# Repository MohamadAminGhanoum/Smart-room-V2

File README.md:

# Smart-room-V2
I have since around 1 year done a smart room, where i made a custom pcb, and salvaged some parts from an old laptop motherboard to be able to control the LED strip that i have and also open and close my curtain, but that was all my thing could do, this time, im planning on making my pcb using jlcpcb instead of for better quality, and im planning on adding a lot more features, such as a screen, CAD and sensor and this stuff.

Note: The Firmware is currently only a test rn, i will upload a working code, once i make this work.

If you are interested, you can check out my V1 of this, with diy pcb: https://github.com/MohamadAminGhanoum/Smart-home

## Schematics:

## PCB + 3d view:

## Fully assembled CAD:

## BOM

|Id |Designator                  |Footprint                                          |Quantity                             |Price in USD|Designation                |Supplier and ref|Link                                                                                                                                                                                                                                                                                                                                               |
|---|----------------------------|---------------------------------------------------|-------------------------------------|------------|---------------------------|----------------|---------------------------------------------------------------------------------------------------------------------------------------------------------------------------------------------------------------------------------------------------------------------------------------------------------------------------------------------------|
|1  |R14,R13,R10,R15,R12,R11     |R_0603_1608Metric                                  |6                                    |0           |4.7k                       |Self-sourced    |https://www.lcsc.com/product-detail/C99782.html?spm=wm.ddx.16.xqy___wm.ddl.ddb.3.ddh&lcsc_vid=T1FYAQdRRlJYVlZTQldcX11eQ1FfUlFUElBWUQFVQgIxVlNeQ1heVlxSRFBfVzsOAxUeFF5JWBEPFBcWGBMaSQgFBAJABAsLWA%3D%3D                                                                                                                                             |
|2  |2pins socket                |PinSocket_1x02_P2.54mm_Vertical                    |15                                   |1.38        |female socket              |LCSC            |https://www.lcsc.com/product-detail/C7499322.html?s_z=n_q_Female%2520Header%25202%2520Position%25202.54mm%2520Pitch%2520Single%2520Row&spm=wm.fly.bg.0.stp&lcsc_vid=T1FYAQdRRlJYVlZTQldcX11eQ1FfUlFUElBWUQFVQgIxVlNeQlBbV1dVTlNWXjsOAxUeFF5JWBYZEEoKFBINSQcJGk4NBhADEA4cHktRTlJADxALGw%3D%3D                                                       |
|3  |R4                          |R_0603_1608Metric                                  |1                                    |0           |1k                         |self-sourced    |https://www.lcsc.com/product-detail/C22548.html?spm=wm.ddx.12.xqy___wm.ddl.ddb.3.ddh&lcsc_vid=T1FYAQdRRlJYVlZTQldcX11eQ1FfUlFUElBWUQFVQgIxVlNeQ1heVlxSRFBfVzsOAxUeFF5JWBEPFBcWGBMaSQgFBAJABAsLWA%3D%3D                                                                                                                                             |
|4  |R                           |R_0603_1608Metric                                  |100                                  |0.51        |0.1R                       |LCSC            |https://www.lcsc.com/product-detail/C3013345.html?s_z=n_q_t_0.1R%25200603&spm=wm.fly.bg.0.stp___wm.ssy.tc.2.tz&lcsc_vid=T1FYAQdRRlJYVlZTQldcX11eQ1FfUlFUElBWUQFVQgIxVlNeQlBbV1VXR1BcXzsOAxUeFF5JWBYZEEoKFBINSQcJGk4NBhADEA4cHktXR1NXSQwSGg0%3D                                                                                                     |
|5  |R9,R16,R5,R7,R3,R2,R17,R18  |R_0603_1608Metric                                  |8                                    |0           |10k                        |self-sourced    |https://www.lcsc.com/product-detail/C2930027.html?spm=wm.ddx.13.xqy___wm.ddl.ddb.0.ddh&lcsc_vid=T1FYAQdRRlJYVlZTQldcX11eQ1FfUlFUElBWUQFVQgIxVlNeQ1heVlxSRFBfVzsOAxUeFF5JWBEPFBcWGBMaSQgFBAJABAsLWA%3D%3D                                                                                                                                           |
|6  |C15,C8,C12,C1               |C_0603_1608Metric                                  |50                                   |1.15        |1uF                        |LCSC            |https://www.lcsc.com/product-detail/C29936.html?s_z=n_q_t_1uf%25200603&spm=wm.fly.bg.0.stp___wm.ssy.tc.0.tz&lcsc_vid=T1FYAQdRRlJYVlZTQldcX11eQ1FfUlFUElBWUQFVQgIxVlNeQlBaX1ZVT1hZUTsOAxUeFF5JWBYZEEoKFBINSQcJGk4NBhYS                                                                                                                              |
|7  |Q1                          |SOT-23                                             |20                                   |0.74        |AO3400A                    |LCSC            |https://www.lcsc.com/product-detail/C347475.html?s_z=n_q_AO3400A&spm=wm.fly.bg.1.stp&lcsc_vid=T1FYAQdRRlJYVlZTQldcX11eQ1FfUlFUElBWUQFVQgIxVlNeQlBaX1dSQ1FcUDsOAxUeFF5JWBYZEEoKFBINSQcJGk4NBhADEA4cHktXRlVcSQwSGg0%3D                                                                                                                               |
|8  |L1                          |L_10.4x10.4_H4.8                                   |5                                    |0.4         |22uH                       |LCSC            |https://www.lcsc.com/product-detail/C5349702.html?s_z=n_q_p_22uH%2520inductor%252010.4x10.4&spm=wm.ssy.bg.0.stp&lcsc_vid=T1FYAQdRRlJYVlZTQldcX11eQ1FfUlFUElBWUQFVQgIxVlNeQlBaX1BQQFBZUDsOAxUeFF5JWBYZEEoKFBINSQcJGk4NBhADEA4cHktXRllfSQwSGg0%3D                                                                                                    |
|9  |E-ink                       |PinSocket_1x08_P2.54mm_Vertical                    |5                                    |1.69        |E-ink waveshare            |lcSC            |https://www.lcsc.com/product-detail/C2848409.html?s_z=n_q_t_Female%2520Header%25208%2520Position%25202.54mm%2520Pitch%2520Single%2520Row&spm=wm.fly.bg.0.stp___wm.ssy.tc.0.tz&lcsc_vid=T1FYAQdRRlJYVlZTQldcX11eQ1FfUlFUElBWUQFVQgIxVlNeQlBbV1ZeT1NZUjsOAxUeFF5JWBYZEEoKFBINSQcJGk4dAgUUFAk%3D                                                      |
|10 |U1                          |ESP32-S3-WROOM-1                                   |2                                    |9.37        |ESP32-S3-WROOM-1           |LCSC            |https://www.lcsc.com/product-detail/C2913197.html?spm=wm.ddx.22.xqy___wm.ddl.ddb.3.ddh&lcsc_vid=T1FYAQdRRlJYVlZTQldcX11eQ1FfUlFUElBWUQFVQgIxVlNeQ1heVlxSRFBfVzsOAxUeFF5JWBEPFBcWGBMaSQgFBAJABAsLWA%3D%3D                                                                                                                                           |
|11 |U6                          |Sensirion_DFN-4_1.5x1.5mm_P0.8mm_SHT4x_NoCentralPad|2                                    |1.91        |SHT4x                      |LCSC            |https://www.lcsc.com/product-detail/C54946589.html?s_z=n_q_sht40&spm=wm.fly.bg.1.stp&lcsc_vid=T1FYAQdRRlJYVlZTQldcX11eQ1FfUlFUElBWUQFVQgIxVlNeQlBaX1xRRlhcUDsOAxUeFF5JWBYZEEoKFBINSQcJGk4dAgUUFAk%3D                                                                                                                                               |
|12 |SW1                         |SW_SPST_TS-1088-xR020                              |1                                    |0           |Boot                       |Self-sourced    |N/A                                                                                                                                                                                                                                                                                                                                                |
|13 |C2,C14,C9,C10,C3,C13        |C_0603_1608Metric                                  |20                                   |1.9         |10uF                       |LCSC            |https://www.lcsc.com/product-detail/C96446.html?s_z=n_q_t_10uF%25200603&spm=wm.fly.bg.0.stp___wm.ssy.tc.0.tz&lcsc_vid=T1FYAQdRRlJYVlZTQldcX11eQ1FfUlFUElBWUQFVQgIxVlNeQlBaXlRTR1NfVDsOAxUeFF5JWBYZEEoKFBINSQcJGk4eFQsCAgIaSgADAwAHC0slQlVXU1JTT1hADxALGw%3D%3D                                                                                     |
|14 |R1                          |R_0603_1608Metric                                  |100                                  |0.39        |6.8k                       |LCSC            |https://www.lcsc.com/product-detail/C844805.html?s_z=n_q_t_6.8k%25200603&spm=wm.fly.bg.2.stp&lcsc_vid=T1FYAQdRRlJYVlZTQldcX11eQ1FfUlFUElBWUQFVQgIxVlNeQlBaXlVUQ1JYVDsOAxUeFF5JWBYZEEoKFBINSQcJGk4dAgUUFAk%3D                                                                                                                                       |
|15 |C16,C11                     |C_0603_1608Metric                                  |2                                    |0           |100nF                      |self-sourced    |https://www.lcsc.com/product-detail/C1591.html?spm=wm.ddx.12.xqy___wm.ddl.ddb.0.ddh&lcsc_vid=T1FYAQdRRlJYVlZTQldcX11eQ1FfUlFUElBWUQFVQgIxVlNeQ1heVlxSRFBfVzsOAxUeFF5JWBEPFBcWGBMaSQgFBAJABAsLWA%3D%3D                                                                                                                                              |
|16 |RV1                         |JST_XH_B3B-XH-A_1x03_P2.50mm_Vertical              |5                                    |2.7         |R_Potentiometer            |aliexpress      |https://www.aliexpress.com/item/1005003161558340.html?spm=a2g0o.detail.0.0.319b257eU1NCPv&mp=1&pdp_npi=6%40dis%21USD%21USD%202.70%21USD%202.70%21%21USD%202.70%21%21%21%4021613ab217851479801197318e100d%2112000024425220398%21ct%21DK%213871794027%21%211%210%21&pdp_ext_f=%7B%22cart2PdpParams%22%3A%7B%22pdpBusinessMode%22%3A%22retail%22%7D%7D|
|17 |BT1                         |BatteryHolder_Keystone_1058_1x2032                 |2                                    |2.74        |Battery_Cell               |LCSC            |https://www.lcsc.com/product-detail/C5470546.html?s_z=n_q_p_BatteryHolder_Keystone_1058_1x2032&spm=wm.ssy.bg.1.stp&lcsc_vid=T1FYAQdRRlJYVlZTQldcX11eQ1FfUlFUElBWUQFVQgIxVlNeQlBaXlZWTlNaVDsOAxUeFF5JWBYZEEoKFBINSQcJGk4NBhADEA4cHktXRlVcSQwSGg0%3D                                                                                                 |
|18 |D2,D3                       |D_SMA                                              |20                                   |0.54        |SS34                       |LCSC            |https://www.lcsc.com/product-detail/C2837271.html?s_z=n_q_t_SS34&spm=wm.fly.bg.3.stp___wm.ssy.tc.0.tz&lcsc_vid=T1FYAQdRRlJYVlZTQldcX11eQ1FfUlFUElBWUQFVQgIxVlNeQlBbV1NfTlJcVjsOAxUeFF5JWBYZEEoKFBINSQcJGk4NBhADEA4cHktXQ1JeSQwSGg0%3D                                                                                                              |
|19 |R8                          |R_0603_1608Metric                                  |100                                  |0.21        |100R                       |LCSC            |https://www.lcsc.com/product-detail/C2906981.html?s_z=n_q_t_100%25CE%25A9%25200603&spm=wm.fly.bg.0.stp___wm.ssy.tc.0.tz&lcsc_vid=T1FYAQdRRlJYVlZTQldcX11eQ1FfUlFUElBWUQFVQgIxVlNeQlBaXldeRlFeUDsOAxUeFF5JWBYZEEoKFBINSQcJGk4dAgUUFAk%3D                                                                                                            |
|20 |R19,R20                     |R_0603_1608Metric                                  |2                                    |0           |33R                        |self-sourced    |https://www.lcsc.com/product-detail/C2909394.html?spm=wm.ddx.11.xqy___wm.ddl.ddb.0.ddh&lcsc_vid=T1FYAQdRRlJYVlZTQldcX11eQ1FfUlFUElBWUQFVQgIxVlNeQ1heVlxSRFBfVzsOAxUeFF5JWBEPFBcWGBMaSQgFBAJABAsLWA%3D%3D                                                                                                                                           |
|21 |C4                          |C_0603_1608Metric                                  |50                                   |0.8         |0.01uF                     |LCSC            |https://www.lcsc.com/product-detail/C100042.html?s_z=n_q_t_10nf%25200603&spm=wm.fly.bg.0.stp___wm.ssy.tc.0.tz&lcsc_vid=T1FYAQdRRlJYVlZTQldcX11eQ1FfUlFUElBWUQFVQgIxVlNeQlBaXlBfRFFeUzsOAxUeFF5JWBYZEEoKFBINSQcJGk4NBhADEA4cHktXRlhXSQwSGg0%3D                                                                                                      |
|22 |C17,C7                      |CP_Elec_6.3x7.7                                    |5                                    |0.55        |220uF                      |LCSC            |https://www.lcsc.com/product-detail/C2827940.html?s_z=n_q_220uF%25206.3x7.7&spm=wm.fly.bg.0.xh&lcsc_vid=T1FYAQdRRlJYVlZTQldcX11eQ1FfUlFUElBWUQFVQgIxVlNeQlBaXlFSR1VbXzsOAxUeFF5JWBYZEEoKFBINSQcJGk4NBhADEA4cHktXRlVcSQwSGg0%3D                                                                                                                     |
|23 |R6                          |R_0603_1608Metric                                  |100                                  |0.3         |3.24k                      |LCSC            |https://www.lcsc.com/product-detail/C22994.html?s_z=n_q_t_3.24k%25200603&spm=wm.fly.bg.0.stp___wm.ssy.tc.0.tz&lcsc_vid=T1FYAQdRRlJYVlZTQldcX11eQ1FfUlFUElBWUQFVQgIxVlNeQlBaXlJUQVBeUjsOAxUeFF5JWBYZEEoKFBINSQcJGk4NBhADEA4cHktXRlVeSQwSGg0%3D                                                                                                      |
|24 |C5,C6                       |C_0603_1608Metric                                  |2                                    |0           |4.7uF                      |self-sourced    |https://www.lcsc.com/product-detail/C6119856.html?spm=wm.ddx.9.xqy___wm.ddl.ddb.3.ddh&lcsc_vid=T1FYAQdRRlJYVlZTQldcX11eQ1FfUlFUElBWUQFVQgIxVlNeQ1heVlxSRFBfVzsOAxUeFF5JWBEPFBcWGBMaSQgFBAJABAsLWA%3D%3D                                                                                                                                            |
|25 |U4                          |SSOP-10-1EP_3.9x4.9mm_P1mm_EP2.1x3.3mm             |4                                    |1.96        |CH224K                     |lcSC            |https://www.lcsc.com/product-detail/C970725.html?s_z=n_q_CH224K&spm=wm.fly.bg.0.stp&lcsc_vid=T1FYAQdRRlJYVlZTQldcX11eQ1FfUlFUElBWUQFVQgIxVlNeQlBaXlNXR1FYXjsOAxUeFF5JWBYZEEoKFBINSQcJGk4NBhADEA4cHktXRlhXSQwSGg0%3D                                                                                                                                |
|26 |U7                          |SOIC-8_3.9x4.9mm_P1.27mm                           |1                                    |0           |Motor controller, AM4969   |self-sourced    |From robot vacuum                                                                                                                                                                                                                                                                                                                                  |
|27 |D1                          |D_SMC                                              |5                                    |1.13        |B340                       |lcSC            |https://www.lcsc.com/product-detail/C110486.html?s_z=n_q_t_b340&spm=wm.fly.bg.8.stp___wm.ssy.tc.0.tz&lcsc_vid=T1FYAQdRRlJYVlZTQldcX11eQ1FfUlFUElBWUQFVQgIxVlNeQlBbV1JWQ1FcVjsOAxUeFF5JWBYZEEoKFBINSQcJGk4eFQsCAgIaSgADAwAHC0slQFVXXldURU8GEwkK                                                                                                     |
|28 |C18                         |C_0603_1608Metric                                  |1                                    |0           |0.1uF                      |self-sourced    |https://www.lcsc.com/product-detail/C1591.html?spm=wm.ddx.12.xqy___wm.ddl.ddb.0.ddh&lcsc_vid=T1FYAQdRRlJYVlZTQldcX11eQ1FfUlFUElBWUQFVQgIxVlNeQ1heVlxSRFBfVzsOAxUeFF5JWBEPFBcWGBMaSQgFBAJABAsLWA%3D%3D                                                                                                                                              |
|29 |U5                          |SOIC-16W_7.5x10.3mm_P1.27mm                        |1                                    |8.77        |DS3231M                    |lcSC            |https://www.lcsc.com/product-detail/C37663.html?spm=wm.gwc.xh.21.tp___wm.fly.ssl.gwc&lcsc_vid=T1FYAQdRRlJYVlZTQldcX11eQ1FfUlFUElBWUQFVQgIxVlNeQlBbV1dVTlNWXjsOAxUeFF5JWBYZEEoKFBINSQcJGk4NBhADEA4cHktRTlJADxALGw%3D%3D                                                                                                                             |
|30 |U3                          |SOT-23-5                                           |5                                    |0.84        |AP2112K-3.3                |lcSC            |https://www.lcsc.com/product-detail/C51118.html?s_z=n_q_AP2112K-3.3&spm=wm.fly.bg.0.stp&lcsc_vid=T1FYAQdRRlJYVlZTQldcX11eQ1FfUlFUElBWUQFVQgIxVlNeQlBaXl1UQVNXXzsOAxUeFF5JWBYZEEoKFBINSQcJGk4NBhADEA4cHktfRVhADxALGw%3D%3D                                                                                                                          |
|31 |U2                          |TI_SO-PowerPAD-8_ThermalVias                       |2                                    |1.98        |TPS5430DDA                 |lcSC            |https://www.lcsc.com/product-detail/C9864.html?s_z=n_q_TPS5430DDA&spm=wm.fly.bg.0.stp&lcsc_vid=T1FYAQdRRlJYVlZTQldcX11eQ1FfUlFUElBWUQFVQgIxVlNeQlBaXl1TRldeXjsOAxUeFF5JWBYZEEoKFBINSQcJGk4NBhADEA4cHktXR1JcSQwSGg0%3D                                                                                                                              |
|32 |J1                          |USB_C_Receptacle_XKB_U262-16XN-4BVC11              |5                                    |0.85        |USB_C_Receptacle_USB2.0_14P|lcSC            |https://www.lcsc.com/product-detail/C165948.html?spm=wm.ddx.6.xqy___wm.ddl.ddb.5.ddh&lcsc_vid=T1FYAQdRRlJYVlZTQldcX11eQ1FfUlFUElBWUQFVQgIxVlNeQ1heVlxSRFBfVzsOAxUeFF5JWBEPFBcWGBMaSQgFBAJABAsLWA%3D%3D                                                                                                                                             |
|33 |SW2                         |SW_SPST_TS-1088-xR020                              |1                                    |0           |EN                         |self-sourced    |N/A                                                                                                                                                                                                                                                                                                                                                |
|34 |PCB                         |JLCPCB                                             |5                                    |4           |JLCPCB                     |JLCPCB          |N/A                                                                                                                                                                                                                                                                                                                                                |
|35 |CAD                         |JLC3DP                                             |1                                    |13          |CAD                        |CAD             |N/A                                                                                                                                                                                                                                                                                                                                                |
|36 |40 pin IDC male to male     |Kiwi electronics                                   |1                                    |4.26        |N/A                        |KIWI electronics|https://www.kiwi-electronics.com/en/40-pin-idc-connector-to-male-jumperwires-20cm-3017?search=male%20to%20male                                                                                                                                                                                                                                     |
|37 |Potentiometer 10k           |Kiwi electronics                                   |2                                    |2.53        |N/A                        |KIWI electronics|https://www.kiwi-electronics.com/en/panel-mount-10k-potentiometer-breadboard-friendly-1783?srsltid=AfmBOorGebntemKDS24jd6JbSDWMUXPPC7Rjy0kmkeHw75-L3x7uk-OW                                                                                                                                                                                        |
|38 |Universal e-Paper Driver HAT|Kiwi electronics                                   |1                                    |13.94       |N/A                        |KIWI electronics|https://www.kiwi-electronics.com/en/universal-e-paper-driver-hat-10267?srsltid=AfmBOoq9rFTDufwvKg7HGxJ_89MUorvNUiUSnOHP5rJiZPefhOlOVlyb                                                                                                                                                                                                            |
|   |                            |                                                   |                                     |            |                           |                |                                                                                                                                                                                                                                                                                                                                                   |
|   |                            |                                                   |                                     |            |                           |                |                                                                                                                                                                                                                                                                                                                                                   |
|   |                            |                                                   |Total price with shipping + vat + tax|107.54      |                           |                |                                                                                                                                                                                                                                                                                                                                                   |

### NOTE: I have used my hardware grant to buy many components, therefore the price will be lower when im going to buy the parts.

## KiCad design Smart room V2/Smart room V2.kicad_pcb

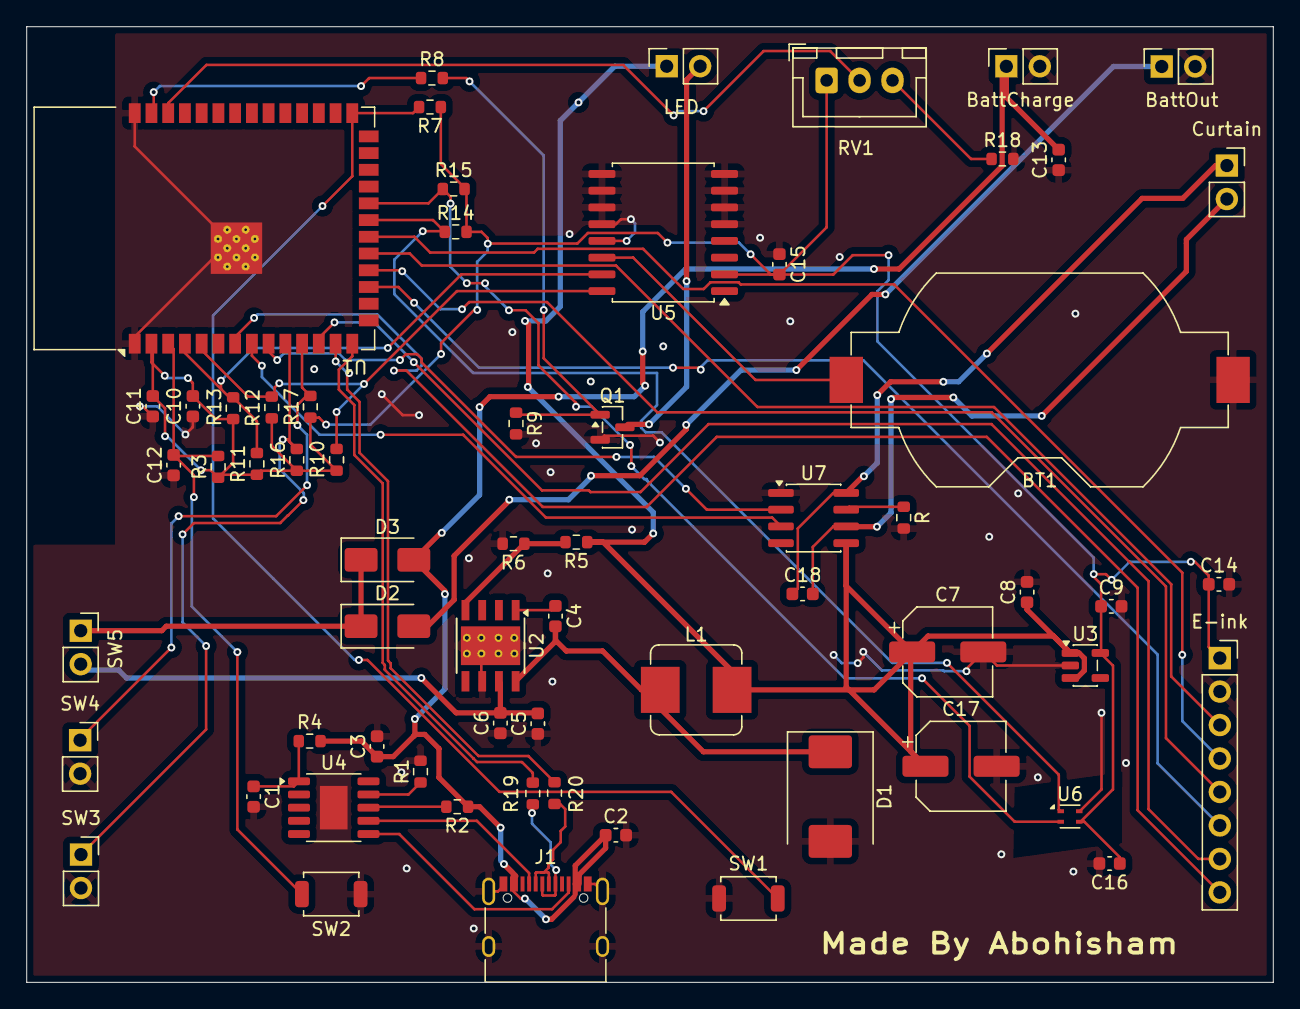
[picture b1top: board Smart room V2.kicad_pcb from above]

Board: 2 copper layers, 94.6 x 72.5 mm, 64 parts (0 on the bottom side), 44 nets.

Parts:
BT1: Battery_Cell; BatteryHolder_Keystone_1058_1x2032
BattCharge: Batt_Charge; PinSocket_1x02_P2.54mm_Vertical
BattOut: Batt_output; PinSocket_1x02_P2.54mm_Vertical
C1, C8, C12, C15: 1uF; C_0603_1608Metric
C2, C3, C9, C10, C13, C14: 10uF; C_0603_1608Metric
C4: 0.01uF; C_0603_1608Metric
C5, C6: 4.7uF; C_0603_1608Metric
C7, C17: 220uF; CP_Elec_6.3x7.7
C11, C16: 100nF; C_0603_1608Metric
C18: 0.1uF; C_0603_1608Metric
Curtain: Curtain; PinSocket_1x02_P2.54mm_Vertical
D1: B340; D_SMC
D2, D3: SS34; D_SMA
E-ink: E-ink waveshare; PinSocket_1x08_P2.54mm_Vertical
J1: USB_C_Receptacle_USB2.0_14P; USB_C_Receptacle_XKB_U262-16XN-4BVC11
L1: 22uH; L_Bourns_SRP7028A_7.3x6.6mm
LED: LED_STRIP; PinSocket_1x02_P2.54mm_Vertical
Q1: AO3400A; SOT-23
R: 0.1R; R_0603_1608Metric
R1: 6.8k; R_0603_1608Metric
R2, R3, R5, R7, R9, R16, R17, R18: 10k; R_0603_1608Metric
R4: 1k; R_0603_1608Metric
R6: 3.24k; R_0603_1608Metric
R8: 100R; R_0603_1608Metric
R10, R11, R12, R13, R14, R15: 4.7k; R_0603_1608Metric
R19, R20: 33R; R_0603_1608Metric
RV1: R_Potentiometer; JST_XH_B3B-XH-A_1x03_P2.50mm_Vertical
SW1: Boot; SW_SPST_TS-1088-xR020
SW2: EN; SW_SPST_TS-1088-xR020
SW3, SW4: SW_Push; PinSocket_1x02_P2.54mm_Vertical
SW5: POWER switch; PinSocket_1x02_P2.54mm_Vertical
U1: ESP32-S3-WROOM-1
U2: TPS5430DDA; TI_SO-PowerPAD-8_ThermalVias
U3: AP2112K-3.3; SOT-23-5
U4: CH224K; SSOP-10-1EP_3.9x4.9mm_P1mm_EP2.1x3.3mm
U5: DS3231M; SOIC-16W_7.5x10.3mm_P1.27mm
U6: SHT4x; Sensirion_DFN-4_1.5x1.5mm_P0.8mm_SHT4x_NoCentralPad
U7: Motor controller, AM4969; SOIC-8_3.9x4.9mm_P1.27mm

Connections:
+3.3V: C9.1, C10.2, C11.2, C14.1, C15.2, C16.1, E-ink.1 (Vcc), R3.1, R7.1, R10.2, R11.1, R12.2, R13.2, R14.2, R15.2, R16.1, R17.2, RV1.1, U1.2 (3V3), U3.5 (VOUT), U5.2 (VCC), U6.3 (VDD)
+5V: C7.1, C8.1, C17.1, L1.2, LED.1, R5.1, U3.1 (VIN), U3.3 (EN), U7.5 (EN1)
/BUSY: E-ink.8 (BUSY), U1.7 (IO7)
/CC1: J1.A5 (CC1), U4.7 (CC1)
/CC2: J1.B5 (CC2), U4.6 (CC2)
/CLK: E-ink.4 (CLK), U1.20 (IO12)
/CS: E-ink.5 (CS), U1.18 (IO10)
/D+: J1.A6 (D+), J1.B6 (D+), R19.2
/D-: J1.A7 (D-), J1.B7 (D-), R20.1
/DC: E-ink.6 (DC), U1.17 (IO9)
/DIN: E-ink.3 (DIN), U1.19 (IO11)
/IO1: R8.1, U1.39 (IO1)
/IO2: RV1.2, U1.38 (IO2)
/IO15: U1.8 (IO15), U7.3 (NC)
/IO16: U1.9 (IO16), U7.2 (GND)
/RST: E-ink.7 (RST), U1.12 (IO8)
/SCL_CLOC: R10.1, R12.1, U1.5 (IO5), U5.16 (SCL)
/SDA_CLOC: R11.2, R13.1, U1.4 (IO4), U5.15 (SDA)
/SHT_SCL: R15.1, U1.22 (IO14), U6.2 (SCL)
/SHT_SDA: R14.1, U1.21 (IO13), U6.1 (SDA)
/V_bat: D2.1 (K), D3.1 (K), SW5.1 (A)
GND: BT1.2 (-), BattCharge.2, BattOut.2, C1.2, C2.2, C3.2, C5.1, C6.1, C7.2, C8.2, C9.2, C10.1, C11.1, C12.1, C13.1, C14.2, C15.1, C16.2, C17.2, D1.2 (A), E-ink.2 (Gnd), J1.A1 (GND), J1.A12 (GND), J1.B1 (GND), J1.B12 (GND), J1.S1 (SHIELD), Q1.2 (S), R.2, R1.2, R6.2, R9.2, R18.2, SW1.1, SW2.1, SW3.2, SW4.2, U1.1 (GND), U1.40 (GND), U1.41 (GND), U2.6 (GND), U2.9 (GNDPAD), U3.2 (GND), U4.11 (GND), U5.5 (GND), U5.6 (GND), U5.7 (GND), U5.8 (GND), U5.9 (GND), U5.10 (GND), U5.11 (GND), U5.12 (GND), U5.13 (GND), U6.4 (VSS), U7.1 (VIN)
LSS: R.1, U7.7 (VOUT2)
unnamed: BT1.1 (+), U5.14 (VBAT)
unnamed: C4.2, D1.1 (K), L1.1, U2.8 (PH)
unnamed: BattOut.1, D2.2 (A)
unnamed: LED.2, Q1.3 (D)
unnamed: C18.1, Curtain.1, U7.8 (VOUT1)
unnamed: C18.2, Curtain.2, U7.6 (NC)
unnamed: Q1.1 (G), R8.2, R9.1
unnamed: R18.1, RV1.3
unnamed: C5.2, C6.2, SW5.2 (B), U2.7 (VIN)
unnamed: C12.2, R3.2, SW2.2, U1.3 (EN)
unnamed: R7.2, SW1.2, U1.27 (IO0)
unnamed: R16.2, SW3.1, U1.10 (IO17)
unnamed: R17.1, SW4.1, U1.11 (IO18)
unnamed: R19.1, U1.14 (USB_D+)
unnamed: R20.2, U1.13 (USB_D-)
unnamed: C4.1, U2.1 (BOOT)
unnamed: R5.2, R6.1, U2.4 (VSENSE)
unnamed: R1.1, U4.9 (CFG1)
unnamed: R2.2, U4.8 (VBUS)
unnamed: C1.1, R4.1, U4.1 (VDD)
VBUS: BattCharge.1, C2.1, C3.1, C13.2, D3.2 (A), J1.A4 (VBUS), J1.A9 (VBUS), J1.B4 (VBUS), J1.B9 (VBUS), R2.1, R4.2

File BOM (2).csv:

Id,Designator,Footprint,Quantity,Price in USD,Designation,Supplier and ref,Link
1,"R14,R13,R10,R15,R12,R11",R_0603_1608Metric,6,0,4.7k,Self-sourced,https://www.lcsc.com/product-detail/C99782.html?spm=wm.ddx.1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
2,2pins socket,PinSocket_1x02_P2.54mm_Vertical,15,1.38,female socket,LCSC,https://www.lcsc.com/product-detail/C7499322.html?s_z=n_q_Fe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
3,R4,R_0603_1608Metric,1,0,1k,self-sourced,https://www.lcsc.com/product-detail/C22548.html?spm=wm.ddx.1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
4,R,R_0603_1608Metric,100,0.51,0.1R,LCSC,https://www.lcsc.com/product-detail/C3013345.html?s_z=n_q_t_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
5,"R9,R16,R5,R7,R3,R2,R17,R18",R_0603_1608Metric,8,0,10k,self-sourced,https://www.lcsc.com/product-detail/C2930027.html?spm=wm.ddx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
6,"C15,C8,C12,C1",C_0603_1608Metric,50,1.15,1uF,LCSC,https://www.lcsc.com/product-detail/C29936.html?s_z=n_q_t_1u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
7,Q1,SOT-23,20,0.74,AO3400A,LCSC,https://www.lcsc.com/product-detail/C347475.html?s_z=n_q_AO3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
8,L1,L_10.4x10.4_H4.8,5,0.4,22uH,LCSC,https://www.lcsc.com/product-detail/C5349702.html?s_z=n_q_p_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
9,E-ink,PinSocket_1x08_P2.54mm_Vertical,5,1.69,E-ink waveshare,lcSC,https://www.lcsc.com/product-detail/C2848409.html?s_z=n_q_t_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
10,U1,ESP32-S3-WROOM-1,2,9.37,ESP32-S3-WROOM-1,LCSC,https://www.lcsc.com/product-detail/C2913197.html?spm=wm.ddx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
11,U6,Sensirion_DFN-4_1.5x1.5mm_P0.8mm_SHT4x_NoCentralPad,2,1.91,SHT4x,LCSC,https://www.lcsc.com/product-detail/C54946589.html?s_z=n_q_s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
12,SW1,SW_SPST_TS-1088-xR020,1,0,Boot,Self-sourced,N/A
13,"C2,C14,C9,C10,C3,C13",C_0603_1608Metric,20,1.9,10uF,LCSC,https://www.lcsc.com/product-detail/C96446.html?s_z=n_q_t_10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
14,R1,R_0603_1608Metric,100,0.39,6.8k,LCSC,https://www.lcsc.com/product-detail/C844805.html?s_z=n_q_t_6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
15,"C16,C11",C_0603_1608Metric,2,0,100nF,self-sourced,https://www.lcsc.com/product-detail/C1591.html?spm=wm.ddx.12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
16,RV1,JST_XH_B3B-XH-A_1x03_P2.50mm_Vertical,5,2.7,R_Potentiometer,aliexpress,https://www.aliexpress.com/item/1005003161558340.html?spm=a2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
17,BT1,BatteryHolder_Keystone_1058_1x2032,2,2.74,Battery_Cell,LCSC,https://www.lcsc.com/product-detail/C5470546.html?s_z=n_q_p_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
18,"D2,D3",D_SMA,20,0.54,SS34,LCSC,https://www.lcsc.com/product-detail/C2837271.html?s_z=n_q_t_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
19,R8,R_0603_1608Metric,100,0.21,100R,LCSC,https://www.lcsc.com/product-detail/C2906981.html?s_z=n_q_t_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
20,"R19,R20",R_0603_1608Metric,2,0,33R,self-sourced,https://www.lcsc.com/product-detail/C2909394.html?spm=wm.ddx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
21,C4,C_0603_1608Metric,50,0.8,0.01uF,LCSC,https://www.lcsc.com/product-detail/C100042.html?s_z=n_q_t_1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
22,"C17,C7",CP_Elec_6.3x7.7,5,0.55,220uF,LCSC,https://www.lcsc.com/product-detail/C2827940.html?s_z=n_q_22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
23,R6,R_0603_1608Metric,100,0.3,3.24k,LCSC,https://www.lcsc.com/product-detail/C22994.html?s_z=n_q_t_3.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
24,"C5,C6",C_0603_1608Metric,2,0,4.7uF,self-sourced,https://www.lcsc.com/product-detail/C6119856.html?spm=wm.ddx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
25,U4,SSOP-10-1EP_3.9x4.9mm_P1mm_EP2.1x3.3mm,4,1.96,CH224K,lcSC,https://www.lcsc.com/product-detail/C970725.html?s_z=n_q_CH2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
26,U7,SOIC-8_3.9x4.9mm_P1.27mm,1,0,"Motor controller, AM4969",self-sourced,From robot vacuum
27,D1,D_SMC,5,1.13,B340,lcSC,https://www.lcsc.com/product-detail/C110486.html?s_z=n_q_t_b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
28,C18,C_0603_1608Metric,1,0,0.1uF,self-sourced,https://www.lcsc.com/product-detail/C1591.html?spm=wm.ddx.12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
29,U5,SOIC-16W_7.5x10.3mm_P1.27mm,1,8.77,DS3231M,lcSC,https://www.lcsc.com/product-detail/C37663.html?spm=wm.gwc.x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
30,U3,SOT-23-5,5,0.84,AP2112K-3.3,lcSC,https://www.lcsc.com/product-detail/C51118.html?s_z=n_q_AP21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
31,U2,TI_SO-PowerPAD-8_ThermalVias,2,1.98,TPS5430DDA,lcSC,https://www.lcsc.com/product-detail/C9864.html?s_z=n_q_TPS54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
32,J1,USB_C_Receptacle_XKB_U262-16XN-4BVC11,5,0.85,USB_C_Receptacle_USB2.0_14P,lcSC,https://www.lcsc.com/product-detail/C165948.html?spm=wm.ddx.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
33,SW2,SW_SPST_TS-1088-xR020,1,0,EN,self-sourced,N/A
34,PCB,JLCPCB,5,4,JLCPCB,JLCPCB,N/A
35,CAD,JLC3DP,1,13,CAD,CAD,N/A
36,40 pin IDC male to male,Kiwi electronics,1,4.26,N/A,KIWI electronics,https://www.kiwi-electronics.com/en/40-pin-idc-connector-to-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
37,Potentiometer 10k,Kiwi electronics,2,2.53,N/A,KIWI electronics,https://www.kiwi-electronics.com/en/panel-mount-10k-potentio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
38,Universal e-Paper Driver HAT,Kiwi electronics,1,13.94,N/A,KIWI electronics,https://www.kiwi-electronics.com/en/universal-e-paper-driver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
,,,,,,,
,,,,,,,
,,,Total price with shipping + vat + tax,107.54,,,
